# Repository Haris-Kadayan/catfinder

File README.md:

catfinder
-
A cat-themed PCB fidget toy with four Cherry MX switches and four LED lights powered by a Seeed Studio XIAO RP2040. It has a Simon Says and a button lights up LED mode. Created for the Hack Club Stasis program.

3D Render
-
This is the 3D render in KiCad with all of the components:

I spent a while with the silkscreen :)

Schematic
-
This is the schematic, which shows all of the connections. This took the least amount of time to make, and to improve organization I used labels:

PCB
-
This is the PCB, this took the most amount of time, the wiring was very dense due to the size of the board. Speaking of the size of the board, it was just under 100mm to save on cost. Because the switches were arragned side by side it was hard to fit everything in that size. It looks messy because of the dual-sided silkscreen:

Code
-
This is the code to the catfinder, this took the second most amount of time. it is programmed in C++ and it has a Simon Says and button lights up LED mode, which is switched by holding all buttons for 5 seconds. I had to figure out how to detect the presses and trigger the LEDs and switches modes. It was kind of hard since im a noob at C++:

BOM
-
| Name                     | Purpose                          | Quantity | Total Cost (USD)                    | Link                                                                                                                                                                                                                                                                                                                                                                                                                                                                                                                                                                                                                                                                                                                                                                        | Distributor |
|--------------------------|----------------------------------|----------|-------------------------------------|-----------------------------------------------------------------------------------------------------------------------------------------------------------------------------------------------------------------------------------------------------------------------------------------------------------------------------------------------------------------------------------------------------------------------------------------------------------------------------------------------------------------------------------------------------------------------------------------------------------------------------------------------------------------------------------------------------------------------------------------------------------------------------|-------------|
| PCB                      | To connect all of the components | 1        | 4                                   | https://jlcpcb.com/                                                                                                                                                                                                                                                                                                                                                                                                                                                                                                                                                                                                                                                                                                                                                         | JLCPCB      |
| Seeed Studio XIAO RP2040 | The brains of the catfinder      | 1        | 9.99                                | https://www.amazon.com/Microcontroller-Dual-Core-MicroPython-CircuitPython-Interfaces/dp/B09NNVNW7M/ref=sr_1_17_sspa?crid=YDSK05QSSMFP&dib=eyJ2IjoiMSJ9.uW11pQUdOACSfChGQK7bo5XLDJn13pOFww-6ggVBcr0bw5BFmugMDxK6MFYelDimANmneBftyqsLi1JmK0bYLdRBasDvrFS4zLIsSvJH8UZsROdrnHvwEq2vhnsDiU5TETXPXBYDobXdIjBNQUMWkMsXblAGoiI6IXCH6_6kKkKxQlk5T3pvAStQ4uRfjbiPXuXCcG5ZDEl3JWSsfKRsriGMFerSPpc2YttIzIQqUiE.gojIAB_DAVjzBCzDz4o5P5pS3dotgHUElO7gej0rcmA&dib_tag=se&keywords=seeed%2Bstudio&qid=1780194149&sprefix=seeed%2Caps%2C138&sr=8-17-spons&sp_csd=d2lkZ2V0TmFtZT1zcF9tdGY&th=1                                                                                                                                                                                               | Amazon      |
| Keycaps                  | The keycap of the catfinder      | 1        | Getting when Hack Boy gets approved | https://www.aliexpress.us/item/3256810533781399.html?spm=a2g0o.detail.0.0.6ef7ODSFODSFNa&mp=1&pdp_npi=6%40dis%21USD%21USD+2.70%21USD+0.99%21%21USD+0.99%21%21%21%4021033d1217808530077753987e944a%2112000053291143010%21ct%21US%217700223557%21%211%210%21&tblci=GihXE9wIgenv&_gl=1*2zvtxk*_gcl_aw*R0NMLjE3Nzk0OTc1MzMuQ2owS0NRand5cjNPQmhEMEFSSXNBTGxvLU9tMU1VMWZ6endObmRJSFhkTVBhcjcxR0hZSzc0U01iNXBCZE95U3VfYzNmR3psNkYwbUpRUWFBbHJmRUFMd193Y0I.*_gcl_dc*R0NMLjE3Nzk0OTc1MzMuQ2owS0NRand5cjNPQmhEMEFSSXNBTGxvLU9tMU1VMWZ6endObmRJSFhkTVBhcjcxR0hZSzc0U01iNXBCZE95U3VfYzNmR3psNkYwbUpRUWFBbHJmRUFMd193Y0I.*_gcl_au*NDUyODkyMjcxLjE3Nzk0OTM2MTE.*_ga*NzY5NTYyMDc3LjE3ODA4NTI1MDc.*_ga_VED1YSGNC7*czE3ODA4NTI1MDYkbzEkZzEkdDE3ODA4NTMwMDUkajEzJGwwJGgw&gatewayAdapt=glo2usa | AliExpress  |
| Brown Switches           | The buttons on the catfinder     | 1        | Getting when Hack Boy gets approved | https://www.aliexpress.us/item/3256811652574937.html?spm=a2g0o.detail.0.0.361c3ba83ba8TU&mp=1&pdp_npi=6%40dis%21USD%21USD+2.99%21USD+2.49%21%21USD+2.49%21%21%21%40210311a017794980043713714e4b30%2112000056744509267%21ct%21US%21-1%21%211%210%21&_gl=1*1120z92*_gcl_aw*R0NMLjE3Nzk0OTc1MzMuQ2owS0NRand5cjNPQmhEMEFSSXNBTGxvLU9tMU1VMWZ6endObmRJSFhkTVBhcjcxR0hZSzc0U01iNXBCZE95U3VfYzNmR3psNkYwbUpRUWFBbHJmRUFMd193Y0I.*_gcl_dc*R0NMLjE3Nzk0OTc1MzMuQ2owS0NRand5cjNPQmhEMEFSSXNBTGxvLU9tMU1VMWZ6endObmRJSFhkTVBhcjcxR0hZSzc0U01iNXBCZE95U3VfYzNmR3psNkYwbUpRUWFBbHJmRUFMd193Y0I.*_gcl_au*NDUyODkyMjcxLjE3Nzk0OTM2MTE.*_ga*MTY1MzkyNjEyMi4xNzc1MjgwMTA1*_ga_VED1YSGNC7*czE3Nzk0OTcyNjUkbzQkZzEkdDE3Nzk0OTgwMDMkajYwJGwwJGgw&gatewayAdapt=glo2usa                           | AliExpress  |
| LEDs                     | To light up the catfinder        | 1        | Already own                         | https://www.amazon.com/California-JOS-50-PCS-Colorful/dp/B0CR886L92/ref=sr_1_3?crid=1N1U0CJT7DOUP&dib=eyJ2IjoiMSJ9.b2ax0uReCWF-zaQ-YkPtSbo0ggyh6DAWuPhHr-3LP9OWquGvSLxPIXtWaoE2lcIeWJz51-yiAkMphWD8Ny66Yw4de8fetmPQqZ7swGGbCwEC3M6gM-oWylw3Jh-mtwxgjFt-AzxhHIf7SoM_PMs_WfMUzQl95CZivc_m1mPmwpRavbYLBEQ5pTEJX-KgjWqPEGBP_z13Rjef0CUbpsuO4GZlzRWirOlEo7m9OfbCTvk.f5meAAjNf8R1PfmsJwBIu5ki2TTyStD7049FUPyMuDA&dib_tag=se&keywords=LED%2B5mm&qid=1780852403&sprefix=led%2B5mm%2Caps%2C345&sr=8-3&th=1                                                                                                                                                                                                                                                                           | Amazon      |
| Resistors                | To limit current to the LEDs     | 1        | Already own                         | https://www.amazon.com/California-JOS-Resistance-CJ50-004-220/dp/B0BDKQSZHM/ref=sr_1_3?crid=1H2D9ZWR3G029&dib=eyJ2IjoiMSJ9.pq8IXZtwkjU13efAoUQ016z7NCJGZDcdcQZ4-GNHnvXvYYcSZMEMnidC7Vpe_2v4GQwxduvHHXCoAdZECMHrla8GAhb4ngAYeSUD5eAjCR0vfB6u7xvCIvFBz6b2YhAoqKokLkxKRbv3Wlmfw5FYrzd3kiCJaFfKLCfsXJcQ4ZmQUof0HznxavbcHVWcr2U1ed2kpTwH1NYC_Yb6tnE1JKkaZa0GYOexexiBN2VyAs0.EL4K2F5WsLvD2URy2zZSxhbNI4gftQhX-G1iVo1-T5Q&dib_tag=se&keywords=resistors%2B220ohm&qid=1780852238&sprefix=resistors%2B220ohm%2Caps%2C139&sr=8-3&th=1                                                                                                                                                                                                                                                 | Amazon      |

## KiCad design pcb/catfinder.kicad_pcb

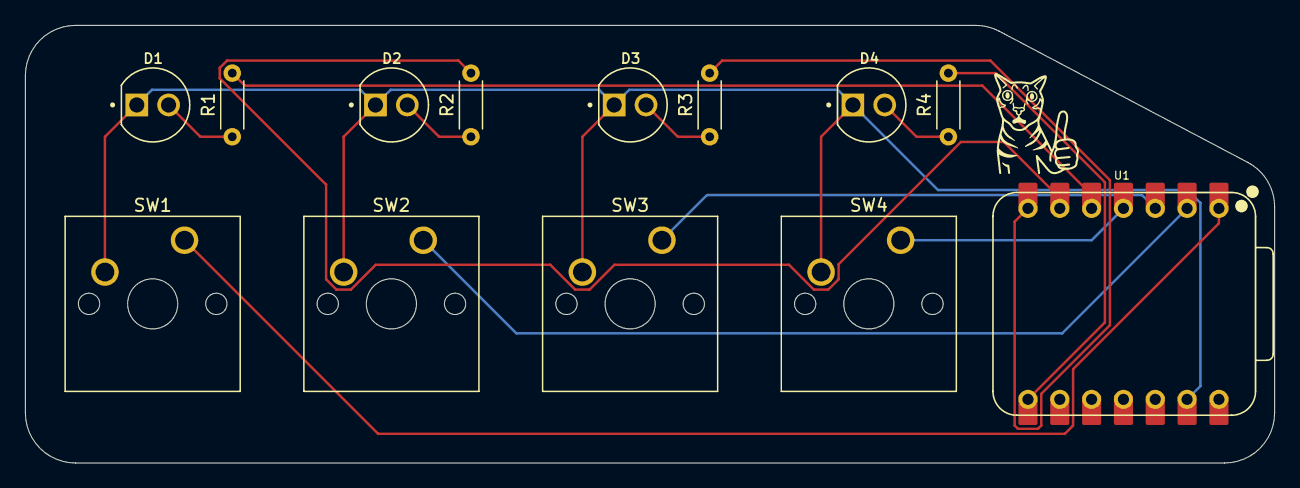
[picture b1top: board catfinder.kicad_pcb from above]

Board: 2 copper layers, 99.7 x 34.9 mm, 13 parts (0 on the bottom side), 13 nets.

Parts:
D1, D2, D3, D4: LED; LEDRD254W57D500H1070
R1, R2, R3, R4: R; R_Axial_DIN0204_L3.6mm_D1.6mm_P5.08mm_Horizontal
SW1, SW2, SW3, SW4: SW_Push; SW_Cherry_MX_1.00u_PCB
U1: XIAO-RP2040-DIP

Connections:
GND: D1.C, D2.C, D3.C, D4.C, SW1.2, SW2.2, SW3.2, SW4.2, U1.13 (GND)
LED1: R1.2, U1.5 (P6_SDA_D4)
LED2: R2.2, U1.6 (P7_SCL_D5)
LED3: R3.2, U1.7 (P0_D6_TX)
LED4: R4.2, U1.8 (P1_D7_RX)
unnamed: D1.A, R1.1
unnamed: D2.A, R2.1
unnamed: D3.A, R3.1
unnamed: D4.A, R4.1
SW1: SW1.1, U1.1 (P26_A0_D0)
SW2: SW2.1, U1.2 (P27_A1_D1)
SW3: SW3.1, U1.3 (P28_A2_D2)
SW4: SW4.1, U1.4 (P29_A3_D3)

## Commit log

2026-05-31 Created PCB folder
2026-05-31 Created code folder
2026-05-31 Add images to README for catfinder project
    Added images of the catfinder from different angles.
2026-05-31 Add additional screenshots to README
2026-05-31 Add new image to README
2026-06-07 Enhance README with additional project details
    Added detailed sections for 3D render, schematic, PCB, and code with images.
2026-06-08 Add BOM table to README
    Added a BOM table listing components, their purposes, quantities, costs, and links.
